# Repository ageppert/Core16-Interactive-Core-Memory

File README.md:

# Core-16-Interactive-Core-Memory-Badge
Weave your own 16 bits of core memory over the top of LEDs to interact with directly using a magnetic wand. This project shares the same codebase as Core64. 

Purchase: https://www.Core64.io

Follow this project at: https://hackaday.io/project/191834-core16-interactive-core-memory-made-smaller

You are in the hardware development repository. Firmware is at https://github.com/ageppert/Core64/releases

# Hardware Version History (latest on top)

v0.2 Logic Board - First production batch

v0.1 Logic Board - Prototype Build

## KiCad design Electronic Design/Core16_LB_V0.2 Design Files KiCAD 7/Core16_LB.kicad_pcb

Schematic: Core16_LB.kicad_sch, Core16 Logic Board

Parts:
C1, C16, C17, C19: 0.1uF; C_0805_2012Metric; LCSC C28233
C7, C8, C9, C13, C14, C15: 220uF; C_1206_3216Metric; LCSC C412252
C10, C12: 1uF; C_0805_2012Metric; LCSC C28323
C11: 0.01uF; C_0805_2012Metric; LCSC C1710
C18: 10uF; C_0805_2012Metric; LCSC C17024
C20, C21, C22, C23: 0.1uF; C_0805_2012Metric; LCSC C396718
CM1: Core_Memory_4x4_Matrix_Front_Facing; core_16_6.75mm_square_front_facing
D1, D3, D9: BAT54CW; SOT-323_SC-70; MPN BAT54CW-7-F; LCSC C83573
D2, D4, D10: BAT54AW; SOT-323_SC-70; MPN BAT54AW-7-F; LCSC C78261
D21, D22, D23, D24, D25, D26, D27, D28, D29, D30, D31, D32, D33, D34, D35, D36: SK6812; 4960_ADA_REV_RGB_LED_short_pads; MPN SK6812-E; Digi-Key_PN 1528-4960-ND
J3: ALT. BATT.; PinSocket_1x02_P2.54mm_Vertical
L1: Core_64_Logo; Core16_w_core_symbol
L3: Core_64_M-+S_Buttons_4mm; Core64-M_-_+_S_Buttons
NT1, NT9, NT11: NetTie_2; NetTie-2_SMD_Pad0.5mm
NT5: GMEM_MON; NetTie-2_THT_Pad0.3mm
NT10: CM_CUR_MON; NetTie-2_SMD_Pad0.5mm
Q1, Q5, Q7, Q9, Q11, Q13, Q17, Q19: MMBT4403LT1G; SOT-23-3; MPN MMBT4403LT1G; Digi-Key_PN MMBT4403LT1GOSCT-ND
Q2, Q6, Q8, Q10, Q12, Q14, Q18, Q20: MMBT4401LT1G; SOT-23-3; MPN MMBT4401LT1G; Digi-Key_PN MMBT4401LT1GOSCT-ND
Q21: NVTR4503NT1G_NMOS_GSD; SOT-23-3; MPN NVTR4503NT1G; LCSC C20917
Q22, Q23: SL3401A; SOT-23-3; MPN SL3401A-TP; LCSC C350311
R1, R2, R5, R6, R7, R8, R9, R10, R11, R12, R13, R14, R17, R18, R19, R20, R28, R46: 470; R_0805_2012Metric; LCSC C17710
R21, R22, R23, R24, R25, R26: 6R8-5%; R_0805_2012Metric; LCSC C17774
R27, R36, R37, R38, R44, R101, R102, R103, R104: 10K; R_0805_2012Metric; LCSC C269724
R30, R31, R41, R42, R43, R54, R55: 1K2; R_0805_2012Metric; LCSC C17379
R32, R33: 68; R_0805_2012Metric; LCSC C17802
R47, R50, R53: 1K5-1%; R_0805_2012Metric; LCSC C4310
R48, R51: 1K8-1%; R_0805_2012Metric; LCSC C17398
R49, R52: 11-1%; R_0805_2012Metric; LCSC C17430
SW1: SK12D07L4B; SK12D07VG4; MPN OS102011MA1QN1; LCSC C480340
U1: PICO W; Pico_SC0915_THRUHOLE_CUTOUTS
U2: M24C02-RMN; SOIC-8_3.9x4.9mm_P1.27mm; MPN M24C02-WMN6TP; LCSC C7562
U7: TLV75533PDBVR; SOT-23-5; MPN ME6211C33M5G-N; LCSC C82942
U8: SN74LV1T125DBVR; SOT-23-5; MPN SN74LV1T125DBVR; LCSC C473338
U9: LM393; SOIC-8_W3.9mm; MPN LM393DT; LCSC C7955
U10: SN74HC02DR; SOIC-14_3.9x8.7mm_P1.27mm; MPN SN74HC02DR; LCSC C350559
U11: SI7210-B-00-IV; SOT-23-5; MPN SI7210-B-00-IV; Digi-Key_PN 336-4068-ND
U12: SI7210-B-02-IV; SOT-23-5; MPN SI7210-B-02-IV; Digi-Key_PN 336-SI7210-B-02-IV-ND
U13: SI7210-B-03-IV; SOT-23-5; MPN SI7210-B-03-IV; Digi-Key_PN 336-SI7210-B-03-IV-ND
U14: SI7210-B-04-IV; SOT-23-5; MPN SI7210-B-04-IV; Digi-Key_PN 336-4056-ND
X8: SAO_conn_SFH11-NBPC-D03-ST-BK; Badgelife-SAOv169-BADGE-2x3; MPN SFH11-NBPC-D03-ST-BK
X9: QWIIC; JST_SH_SM04B-SRSS-TB_1x04-1MP_P1.00mm_Horizontal; MPN SM04B-SRSS-TB; LCSC C160404

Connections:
3V3: C1.1, C12.1, C13.1, C14.1, C15.1, C17.1, C18.1, C19.1, C20.1, C21.1, C22.1, C23.1, NT10.1, R30.1, R31.1, R48.1, R51.1, R54.1, R55.1, R101.1, R102.1, R103.1, R104.1, U2.1 (E0), U2.2 (E1), U2.3 (E2), U2.8 (VCC), U7.5 (OUT), U9.8 (V+), U10.14 (VCC), U11.4 (VDD), U12.4 (VDD), U13.4 (VDD), U14.4 (VDD), X8.1 (3V3), X9.2
5V0: C7.1, C8.1, C9.1, C10.1, C16.1, D21.1 (VDD), D22.1 (VDD), D23.1 (VDD), D24.1 (VDD), D25.1 (VDD), D26.1 (VDD), D27.1 (VDD), D28.1 (VDD), D29.1 (VDD), D30.1 (VDD), D31.1 (VDD), D32.1 (VDD), D33.1 (VDD), D34.1 (VDD), D35.1 (VDD), D36.1 (VDD), NT11.2, Q23.3 (D), U7.1 (IN), U7.3 (EN), U8.5 (VCC)
5VUSB: NT9.2, Q23.1 (G), SW1.1 (A)
+BATT: J3.1, SW1.3 (C)
+VSW: NT11.1, Q22.2 (S), R36.2
-BATT: C1.2, C7.2, C8.2, C9.2, C10.2, C11.2, C12.2, C13.2, C14.2, C15.2, C16.2, C17.2, C18.2, C19.2, C20.2, C21.2, C22.2, C23.2, D21.3 (GND), D22.3 (GND), D23.3 (GND), D24.3 (GND), D25.3 (GND), D26.3 (GND), D27.3 (GND), D28.3 (GND), D29.3 (GND), D30.3 (GND), D31.3 (GND), D32.3 (GND), D33.3 (GND), D34.3 (GND), D35.3 (GND), D36.3 (GND), J3.2, Q21.2 (S), R27.1, R38.2, R44.2, R50.2, R53.2, U1.3 (GND), U1.8 (GND), U1.13 (GND), U1.18 (GND), U1.23 (GND), U1.28 (GND), U1.33 (AGND/GND), U1.38 (GND), U2.4 (VSS), U2.7 (~WC), U7.2 (GND), U8.1 (/OE), U8.3 (GND), U9.4 (V-), U10.7 (GND), U11.2 (GND), U12.2 (GND), U13.2 (GND), U14.2 (GND), X8.2 (GND), X9.1
/ADC0: R41.1, U1.31 (I2C1_SDA/ADC0/GP26)
/ADC0_BUFF: R37.1, R38.1, R41.2
/ADC1: R42.1, U1.32 (I2C1_SCL/ADC1/GP27)
/ADC2: R43.1, U1.34 (ADC2/GP28)
/CA_SENSE_1_OUT: R55.2, U9.7, U10.3
/CA_SENSE_2_OUT: R54.2, U9.1, U10.2
/CM_EN: R27.2, R28.1, U1.26 (I2C0_SDA/GP20)
/CM_Q1N: NT1.2, R2.2, U1.4 (I2C1_SDA/SPI0_SCK/GP2)
/CM_Q1P: R1.2, U1.2 (UART0_RX/I2C0_SCL/GPI0_CSn/GP1)
/CM_Q3N: R6.2, U1.6 (UART1_TX/I2C0_SDA/SPI0_RX/GP4)
/CM_Q3P: R5.2, U1.5 (I2C1_SCL/SPI0_TX/GP3)
/CM_Q4N: R8.2, U1.9 (I2C1_SDA/SPI0_SCK/GP6)
/CM_Q4P: R7.2, U1.7 (UART1_RX/I2C0_SCL/SPI0_CSn/GP5)
/CM_Q5N: R10.2, U1.11 (UART1_TX/I2C0_SDA/SPI1_RX/GP8)
/CM_Q5P: R9.2, U1.10 (I2C1_SCL/SPI0_TX/GP7)
/CM_Q6N: R12.2, U1.16 (UART0_TX/I2C0_SDA/GPI1_RX/GP12)
/CM_Q6P: R11.2, U1.12 (UART1_RX/I2C0_SCL/SPI1_CSn/GP9)
/CM_Q7N: R14.2, U1.19 (I2C1_SDA/SPI1_SCK/GP14)
/CM_Q7P: R13.2, U1.17 (UART0_RX/I2C0_SCL/SPI1_CSn/GP13)
/CM_Q9N: R18.2, U1.21 (UART0_TX/I2C0_SDA/SPI0_RX/GP16)
/CM_Q9P: R17.2, U1.20 (I2C1_SCL/SPI1_TX/GP15)
/CM_Q10N: R20.2, U1.25 (I2C1_SCL/SPI0_TX/GP19)
/CM_Q10P: R19.2, U1.24 (I2C1_SDA/SPI0_SCK/GP18)
/CM_SENSE_1_IN: CM1.17 (S1), R47.1, R52.2, R53.1, U9.5 (+)
/CM_SENSE_2_IN: CM1.18 (S2), R47.2, R49.2, R50.1, U9.3 (+)
/CM_SENSE_PULSE: U1.27 (I2C0_SCL/GP21), U10.10, U10.11
/CM_SENSE_RESET: U1.1 (UART0_TX/I2C0_SDA/SPI0_RX/GP0), U10.8
/GPIO1_SAO1: NT1.1, X8.5 (GPIO1)
/GPIO2_SAO2: U1.22 (UART0_RX/I2C0_SCL/SPI0_CSn/GP17), X8.6 (GPIO2)
/I2C_3V3_SCL: R32.2, U2.6 (SCL), U11.3 (SCL), U12.3 (SCL), U13.3 (SCL), U14.3 (SCL), X8.4 (SCL), X9.4
/I2C_3V3_SDA: R33.1, U2.5 (SDA), U11.1 (SDA), U12.1 (SDA), U13.1 (SDA), U14.1 (SDA), X8.3 (SDA), X9.3
/I2C_CLOCK: R30.2, R32.1, U1.15 (I2C1_SCL/SPI1_TX/GP11)
/I2C_DATA: R31.2, R33.2, U1.14 (I2C1_SDA/SPI1_SCK/GP10)
/LED_ARY_3V3_SIG: U1.29 (GP22), U8.2 (A)
/LED_ARY_5V0_SIG: D21.4 (DIN), R46.1
/XB0: CM1.12 (XB0), D1.1, D2.2
/XB1: CM1.11 (XB1), D1.2, D2.1
/XB2: CM1.10 (XB2), D3.1, D4.2
/XB3: CM1.9 (XB3), D3.2, D4.1
/XT0: CM1.1 (XT0), R21.2
/XT1: CM1.2 (XT1), R22.1
/XT2: CM1.3 (XT2), R23.1
/XT3: CM1.4 (XT3), R24.1
/YL0: CM1.16 (YL0), D9.2, D10.1
/YL0,2: CM1.5 (YR0), CM1.7 (YR2)
/YL1: CM1.15 (YL1), D9.1, D10.2
/YL1,3: CM1.6 (YR1), CM1.8 (YR3)
/YL2: CM1.14 (YL2), R25.1
/YL3: CM1.13 (YL3), R26.1
GMEM: NT5.2, Q2.2 (E), Q6.2 (E), Q8.2 (E), Q10.2 (E), Q12.2 (E), Q14.2 (E), Q18.2 (E), Q20.2 (E), R43.2
unnamed: D21.2 (DOUT), D22.4 (DIN)
unnamed: D22.2 (DOUT), D23.4 (DIN)
unnamed: D23.2 (DOUT), D24.4 (DIN)
unnamed: D24.2 (DOUT), D25.4 (DIN)
unnamed: D25.2 (DOUT), D26.4 (DIN)
unnamed: D26.2 (DOUT), D27.4 (DIN)
unnamed: D27.2 (DOUT), D28.4 (DIN)
unnamed: D28.2 (DOUT), D29.4 (DIN)
unnamed: D29.2 (DOUT), D30.4 (DIN)
unnamed: D30.2 (DOUT), D31.4 (DIN)
unnamed: D31.2 (DOUT), D32.4 (DIN)
unnamed: D32.2 (DOUT), D33.4 (DIN)
unnamed: D33.2 (DOUT), D34.4 (DIN)
unnamed: D34.2 (DOUT), D35.4 (DIN)
unnamed: D35.2 (DOUT), D36.4 (DIN)
unnamed: Q1.1 (B), R1.1
unnamed: D2.3, D4.3, Q1.3 (C)
unnamed: Q2.1 (B), R2.1
unnamed: D1.3, D3.3, Q2.3 (C)
unnamed: Q5.1 (B), R5.1
unnamed: Q5.3 (C), Q6.3 (C), R21.1
unnamed: Q6.1 (B), R6.1
unnamed: Q7.1 (B), R7.1
unnamed: Q7.3 (C), Q8.3 (C), R22.2
unnamed: Q8.1 (B), R8.1
unnamed: Q9.1 (B), R9.1
unnamed: Q10.1 (B), R10.1
unnamed: Q9.3 (C), Q10.3 (C), R23.2
unnamed: Q11.1 (B), R11.1
unnamed: Q11.3 (C), Q12.3 (C), R24.2
unnamed: Q12.1 (B), R12.1
unnamed: Q13.1 (B), R13.1
unnamed: D10.3, Q13.3 (C)
unnamed: Q14.1 (B), R14.1
unnamed: D9.3, Q14.3 (C)
unnamed: Q17.1 (B), R17.1
unnamed: Q17.3 (C), Q18.3 (C), R25.2
unnamed: Q18.1 (B), R18.1
unnamed: Q19.1 (B), R19.1
unnamed: Q19.3 (C), Q20.3 (C), R26.2
unnamed: Q20.1 (B), R20.1
unnamed: NT5.1, Q21.3 (D)
unnamed: Q21.1 (G), R28.2
unnamed: Q22.3 (D), SW1.2 (B)
unnamed: Q22.1 (G), R44.1
unnamed: R36.1, R37.2
unnamed: C11.1, U7.4 (NC)
unnamed: R46.2, U8.4 (Y)
unnamed: R51.2, R52.1, U9.2 (-)
unnamed: R48.2, R49.1, U9.6 (_)
unnamed: U10.1, U10.5, U10.6
unnamed: U10.4, U10.12
unnamed: U10.9, U10.13
unnamed: R101.2, U11.5 (ALERT)
unnamed: R102.2, U12.5 (ALERT)
unnamed: R103.2, U13.5 (ALERT)
unnamed: R104.2, U14.5 (ALERT)
PICO_3V3OUT: U1.35 (ADC_VREF), U1.36 (3V3OUT)
PICO_VBUS: NT9.1, U1.40 (VBUS)
PICO_VSYS: Q23.2 (S), U1.39 (VSYS)
VMEM: NT10.2, Q1.2 (E), Q5.2 (E), Q7.2 (E), Q9.2 (E), Q11.2 (E), Q13.2 (E), Q17.2 (E), Q19.2 (E), R42.2

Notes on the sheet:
Bits 3-0
SILKSCREEN FRONT
INCLUDED:
QxP (PNP) is normally high, low to activate matrix transistor.
AMBIENT PROX. SENSOR OLED AND!XOR IO Exp. MCP23017 AND!XOR EEPROM AT24C32r NFC CLICK PN7120
P-CHNL
C7-9,10-15 D - H - J3 JP - NT9,10,11 Q22-23 R44 SW1 TP - U7 X -
HACKER PLAYGROUND
https://hackaday.io/project/175182-simple-add-ons-sao using Sullins SFH11-NBPC-D03-ST-BK female header https://www.digikey.com/product-detail/en/sullins-connector-solutions/ SFH11-NBPC-D03-ST-BK/S9717-ND/4558818
DIGITAL LOGIC GROUND
SAO #1 SIMPLE ADD-ONS
Bits 15-12
Core16: Removed battery access along with the stacked headers.
I2C ADDRESS TABLE
This diode is built-in to the Pico.
C16 D21-36 H - J - JP - NT - Q - R36-30, 41-43, 46, 101-104 SW - TP - U8,11-14 X8-9
POWER FLOW MORE DETAIL IN CORE64 USER GUIDE
Rds(ON)=0.1
Pico has incoming USB power/programming on board.
COL 0
B_M
DNI
PICO MICROCONTROLLER
C - D1-4, 9-10 H - J - JP - NT5 Q1-20, 21 R1-20, 21-26, 27-28 SW - TP - U - X -
HALL SENSORS
Core16: Removed net-ties and core column 0 / row 0 voltage monitors.
L1-???
SENSE SIGNAL OUTPUT LATCH
NOR -> NOT -> RS LATCH
CORE MATRIX ROW DRIVERS
Pixels 0-3
TWO POWER INPUT SOURCES SELECTED BY SPDT SWITCH. Power Switch ON (BAT), USB cable is NOT connected: P-FET (gate is low) conducts 5V0 (or less if the battery is less than about 5.2V) so that PICO_SYS is powered. PICO_VBUS is not energized because of built-in Zener diode on the Pico. Power Switch OFF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
Default: VMEM (3V3_MON)
CORE MATRIX BOTTOM COLUMN DRIVERS
CORE16: flipped switch inputs so UP is ON when installed on PCB
SOT-23-5 .238VDROP@500mA
Core16: Moved LED driver to lower left sheet.
QxN (NPN) is normally low, high to activate matrix transistor.
BOARD ID AND S/N
OFF (USB)

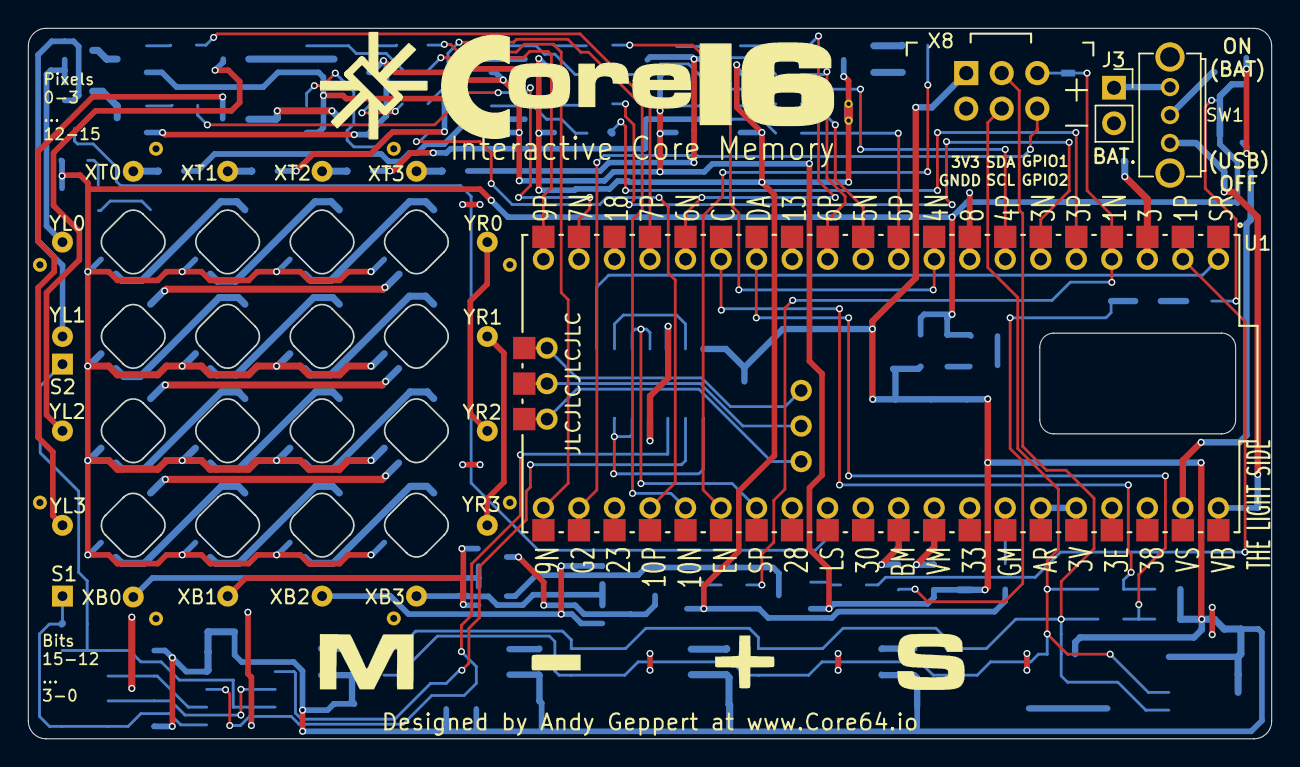
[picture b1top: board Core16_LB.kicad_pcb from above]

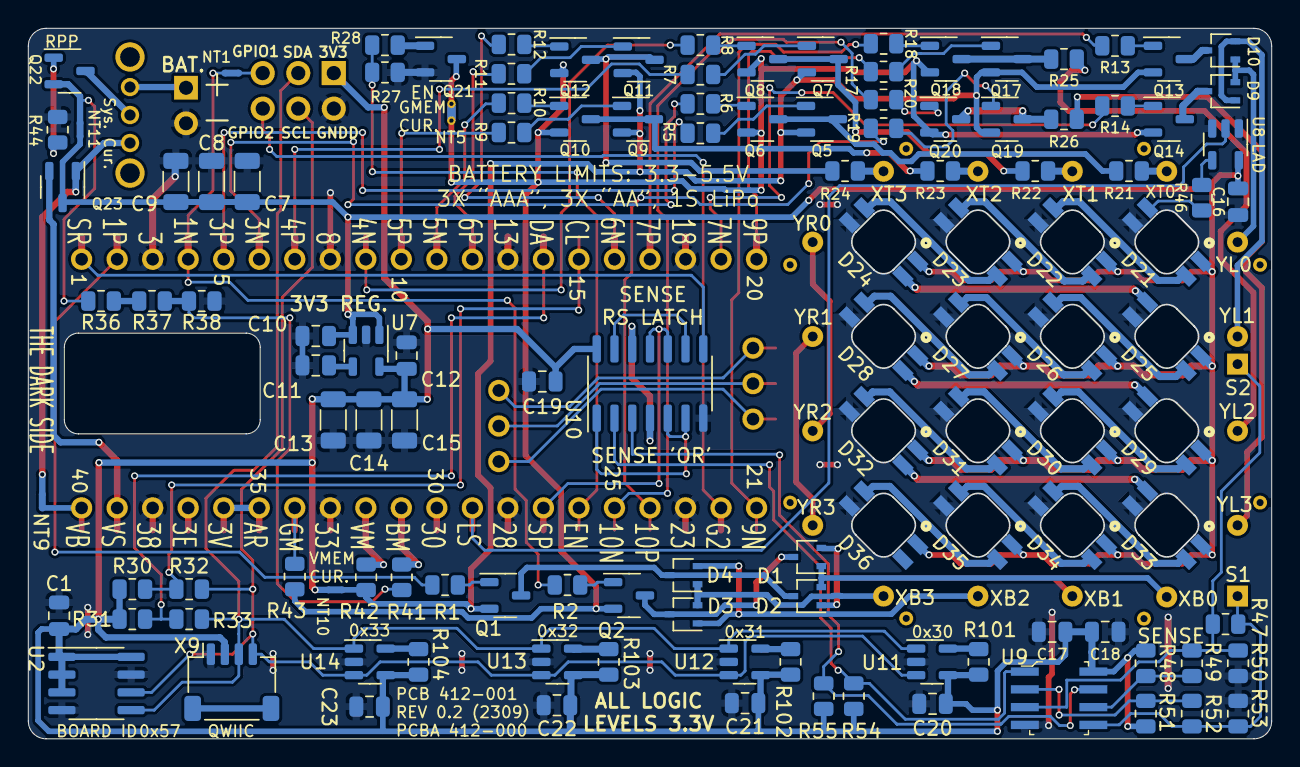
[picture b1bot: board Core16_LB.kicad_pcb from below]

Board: 2 copper layers, 88.8 x 50.7 mm, 130 parts (107 on the bottom side), 117 nets.

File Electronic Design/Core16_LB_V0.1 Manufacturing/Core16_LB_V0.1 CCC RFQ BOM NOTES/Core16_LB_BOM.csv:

"Reference","Value","Footprint","Description","Digi-Key_PN","Insert","LCSC","MPN","MPN(Secondary)","Manufacturer","Manufacturer(Secondary)","Mouser Part Number","Value_Modifier","Qty"
"C1, C16, C17, C19-C23","0.1uF","Capacitor_SMD:C_0805_2012Metric","Capacitor 0805 0.1uF","","YES","-- mixed values --","","","","","","X7R ceramic","8"
"C7-C9, C13-C15","220uF","Capacitor_SMD:C_1206_3216Metric","Capacitor 1206 220uF","","YES","C412252","","","","","","","6"
"C10, C12","1uF","Capacitor_SMD:C_0805_2012Metric","Capacitor 0805 1uF","","YES","C28323","","","","","","","2"
"C11","0.01uF","Capacitor_SMD:C_0805_2012Metric","Capacitor 0805 0.01uF","","YES","C1710","","","","","","","1"
"C18","10uF","Capacitor_SMD:C_0805_2012Metric","Capacitor 0805 10uF","","YES","C17024","","","","","","","1"
"CM1","Core_Memory_4x4_Matrix_Front_Facing","Core_64_KiCad_Library:core_16_6.75mm_square_front_facing","","","NO","","","","","","","","1"
"D1, D3, D9","BAT54CW","Package_TO_SOT_SMD:SOT-323_SC-70","DIODE ARRAY SCHOTTKY 30V ","BAT54CW-FDITR-ND","YES","C83573","BAT54CW-7-F","","Diodes Inc.","","","","3"
"D2, D4, D10","BAT54AW","Package_TO_SOT_SMD:SOT-323_SC-70","DIODE ARRAY SCHOTTKY 30V ","BAT54AW-FDITR-ND","YES","C78261","BAT54AW-7-F","","Diodes Inc.","","","","3"
"D21-D36","SK6812","Core_64_KiCad_Library:4960_ADA_REV_RGB_LED_short_pads","NEOPIXEL REVERSE MOUNT RGB LED","1528-4960-ND","NO","","SK6812-E","","DONGGUAN OPSCO OPTOELECTRONICS","","485-4960","","16"
"J3","ALT. BATT.","Connector_PinSocket_2.54mm:PinSocket_1x02_P2.54mm_Vertical","","","NO","","","","","","","","1"
"L1","Core_64_Logo","Core_64_KiCad_Library:Core16_w_core_symbol","","","NO","","","","","","","","1"
"L3","Core_64_M-+S_Buttons_4mm","Core_64_KiCad_Library:Core64-M_-_+_S_Buttons","","","NO","","","","","","","","1"
"NT1, NT9, NT11","NetTie_2","NetTie:NetTie-2_SMD_Pad0.5mm","","","NO","","","","","","","","3"
"NT5","GMEM_MON","NetTie:NetTie-2_THT_Pad0.3mm","","","NO","","","","","","","","1"
"NT10","CM_CUR_MON","NetTie:NetTie-2_SMD_Pad0.5mm","","","NO","","","","","","","","1"
"Q1, Q5, Q7, Q9, Q11, Q13, Q17, Q19","MMBT4403LT1G","Package_TO_SOT_SMD:SOT-23-3","TRANS PNP 40V 0.6A SOT23","MMBT4403LT1GOSCT-ND","YES","C78864","MMBT4403LT1G","MMBT4403-7-F","ON Semiconductor","Diodes Inc.","","","8"
"Q2, Q6, Q8, Q10, Q12, Q14, Q18, Q20","MMBT4401LT1G","Package_TO_SOT_SMD:SOT-23-3","TRANS NPN 40V 0.6A SOT23","MMBT4401LT1GOSCT-ND","YES","C31776","MMBT4401LT1G","MMBT4401-7-F","ON Semiconductor","Diodes Inc.","","","8"
"Q21","NVTR4503NT1G_NMOS_GSD","Package_TO_SOT_SMD:SOT-23-3","MOSFET N-CHNL GSD LOW RDS(ON)","NVTR4503NT1GOSTR-ND","YES","C20917","NVTR4503NT1G","IRLML2030TRPBF","ON Semiconductor","Infineon Technologies","","","1"
"Q22, Q23","SL3401A","Package_TO_SOT_SMD:SOT-23-3","P-Channel 30V 4.2A 2V @ 250uA 50mΩ @ 4.2A,10V 1.4W SOT-23 MOSFETs RoHS","353-SL3401A-TPTR-ND","YES","C350311","SL3401A-TP","","Micro Commercial Co","","","","2"
"R1, R2, R5-R14, R17-R20, R28, R46","470","Resistor_SMD:R_0805_2012Metric","RES 470 OHM","","YES","C17710","","","","","","10%","18"
"R21-R26","6R8-5%","Resistor_SMD:R_0805_2012Metric","RES  6.8 OHM 1/8W","","YES","C17774","","","","","","5%","6"
"R27, R36-R38, R44","10k","Resistor_SMD:R_0805_2012Metric","RES 10K OHM","","YES","C17414","","","","","","-- mixed values --","5"
"R30, R31, R54, R55","1K2","Resistor_SMD:R_0805_2012Metric","RES 1.2K OHM","","YES","C17379","","","","","","10%","4"
"R32, R33","68","Resistor_SMD:R_0805_2012Metric","RES 68 OHM","","YES","C17802","","","","","","10%","2"
"R41-R43","1k2","Resistor_SMD:R_0805_2012Metric","RES 10K OHM","","YES","C17379","","","","","","20%","3"
"R47, R50, R53","1K5-1%","Resistor_SMD:R_0805_2012Metric","RES 1.5K OHM","","YES","C4310","","","","","","1%","3"
"R48, R51","1K8-1%","Resistor_SMD:R_0805_2012Metric","RES 1.8K OHM","","YES","C17398","","","","","","1%","2"
"R49, R52","11-1%","Resistor_SMD:R_0805_2012Metric","RES 1 OHM","","YES","C17430","","","","","","1%","2"
"R101-R104","10K","Resistor_SMD:R_0805_2012Metric","RES 10K OHM","","YES","C269724","","","","","","10%","4"
"SW1","SK12D07L4B","Switch_XKB_SK12D07VG4_SK12D07L4B:SK12D07VG4","Switch","CKN9559-ND","YES","C480340","OS102011MA1QN1","","C&K","","","","1"
"U1","PICO W","Core_64_KiCad_Library:Pico_SC0915_THRUHOLE_CUTOUTS","Raspberry Pi Pico W","","NO","","","","","","","","1"
"U2","M24C02-RMN","Package_SO:SOIC-8_3.9x4.9mm_P1.27mm","IC EEPROM 2KBIT I2C 400KHZ 8SOIC","497-8552-2-ND","YES","C7562","M24C02-WMN6TP","","STMicroelectronics","","","","1"
"U7","SSP9193-33M5R","Package_TO_SOT_SMD:SOT-23-5","Fixed 3.3V 300mV @ 300mA SOT-23-5 Dropout Regulators(LDO) RoHS","296-TPS7A0533PDBVRTR-ND","YES","C411022","SGM2007-3.3XN5_TR","TPS7A0533PDBVR","SG Micro","TI","","","1"
"U8","SN74LV1T125DBVR","Package_TO_SOT_SMD:SOT-23-5","IC BUF NON-INVERT 5.5V SOT23-5","296-37172-2-ND","YES","C473338","SN74LV1T125DBVR","M74VHC1GT125DT1G","Texas Instruments","OnSemi","","","1"
"U9","LM393","Core_64_KiCad_Library:SOIC-8_W3.9mm","IC COMPARATOR LP DUAL 8-SOIC","497-1593-2-ND","YES","C7955","LM393DT","LM393DR","STMicroelectronics","Rohm","","","1"
"U10","SN74HC02DR","Package_SO:SOIC-14_3.9x8.7mm_P1.27mm","IC GATE NOR 4CH 2-INP 14SOIC","296-1188-2-ND","YES","C350559","SN74HC02DR","","Texas Instruments","","","","1"
"U11","SI7210-B-00-IV","Package_TO_SOT_SMD:SOT-23-5","Si7210 Series I2C Hall Effect Magnetic Position and Temperature Sensor","336-4068-ND","YES","","SI7210-B-00-IV","","Silicon Labs","","","","1"
"U12","SI7210-B-02-IV","Package_TO_SOT_SMD:SOT-23-5","Si7210 Series I2C Hall Effect Magnetic Position and Temperature Sensor","336-SI7210-B-02-IV-ND","YES","","SI7210-B-02-IV","","Silicon Labs","","","","1"
"U13","SI7210-B-03-IV","Package_TO_SOT_SMD:SOT-23-5","Si7210 Series I2C Hall Effect Magnetic Position and Temperature Sensor","336-SI7210-B-03-IV-ND","YES","","SI7210-B-03-IV","","Silicon Labs","","","","1"
"U14","SI7210-B-04-IV","Package_TO_SOT_SMD:SOT-23-5","Si7210 Series I2C Hall Effect Magnetic Position and Temperature Sensor","336-4056-ND","YES","","SI7210-B-04-IV","","Silicon Labs","","","","1"
"X8","SAO_conn_SFH11-NBPC-D03-ST-BK","Core_64_KiCad_Library:Badgelife-SAOv169-BADGE-2x3","CONN HDR 6POS KEYED SOCKET 0.1 T.H.","","NO","","SFH11-NBPC-D03-ST-BK","","Sullins","","","","1"
"X9","QWIIC","Connector_JST:JST_SH_SM04B-SRSS-TB_1x04-1MP_P1.00mm_Horizontal","JST_SH_SM04B-SRSS-TB_1x04","455-SM04B-SRSS-TBTR-ND","YES","C160404","SM04B-SRSS-TB","","JST","","","","1"

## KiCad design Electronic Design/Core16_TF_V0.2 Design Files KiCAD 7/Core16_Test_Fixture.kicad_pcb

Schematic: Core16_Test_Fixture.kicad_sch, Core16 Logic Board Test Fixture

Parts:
C1: 0.1uF; C_0805_2012Metric; LCSC C28233
CM1, CM2: Core_Memory_4x4_Matrix_Front_Facing; core_16_6.75mm_square_front_facing
J1, J2: ALT. BATT.; PinSocket_1x02_P2.54mm_Vertical
J3: Conn_01x18_Socket; PinHeader_1x18_P2.54mm_Vertical
J4, J5: Conn_01x20_Socket; PinHeader_1x20_P2.54mm_Vertical
J6: Conn_01x05_Socket; PinHeader_1x05_P2.54mm_Vertical
J7: Conn_01x06_Socket; PinHeader_1x06_P2.54mm_Vertical
J8: Conn_01x04_Socket; PinHeader_1x04_P2.54mm_Vertical
SW1, SW2: SK12D07L4B; SK12D07VG4; MPN OS102011MA1QN1; LCSC C480340
U1, U2: PICO W; Pico_SC0915_THRUHOLE_CUTOUTS
U3: M24C02-RMN; SOIC-8_3.9x4.9mm_P1.27mm; MPN M24C02-WMN6TP; LCSC C7562
X1, X2: SAO_conn_SFH11-NBPC-D03-ST-BK; Badgelife-SAOv169-BADGE-2x3; MPN SFH11-NBPC-D03-ST-BK
X3: QWIIC; JST_SH_SM04B-SRSS-TB_1x04-1MP_P1.00mm_Horizontal; MPN SM04B-SRSS-TB; LCSC C160404

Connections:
/3V3: C1.1, J7.2, J8.2, U3.2 (E1), U3.3 (E2), U3.8 (VCC), X1.1 (3V3), X2.1 (3V3), X3.2
/3V3_EN: J5.17, U1.37 (3V3_EN), U2.37 (3V3_EN)
/+BATT: J1.1, J2.1, J6.2
/-BATT: J1.2, J2.2, J6.1
/ADC0: J5.11, U1.31 (I2C1_SDA/ADC0/GP26), U2.31 (I2C1_SDA/ADC0/GP26)
/ADC1: J5.12, U1.32 (I2C1_SCL/ADC1/GP27), U2.32 (I2C1_SCL/ADC1/GP27)
/ADC2: J5.14, U1.34 (ADC2/GP28), U2.34 (ADC2/GP28)
/ADC_REF: J5.15, J5.16, U1.35 (ADC_VREF), U1.36 (3V3OUT), U2.35 (ADC_VREF), U2.36 (3V3OUT)
/CM_EN: J5.6, U1.26 (I2C0_SDA/GP20), U2.26 (I2C0_SDA/GP20)
/CM_Q1N: J4.4, U1.4 (I2C1_SDA/SPI0_SCK/GP2), U2.4 (I2C1_SDA/SPI0_SCK/GP2)
/CM_Q1P: J4.2, U1.2 (UART0_RX/I2C0_SCL/GPI0_CSn/GP1), U2.2 (UART0_RX/I2C0_SCL/GPI0_CSn/GP1)
/CM_Q3N: J4.6, U1.6 (UART1_TX/I2C0_SDA/SPI0_RX/GP4), U2.6 (UART1_TX/I2C0_SDA/SPI0_RX/GP4)
/CM_Q3P: J4.5, U1.5 (I2C1_SCL/SPI0_TX/GP3), U2.5 (I2C1_SCL/SPI0_TX/GP3)
/CM_Q4N: J4.9, U1.9 (I2C1_SDA/SPI0_SCK/GP6), U2.9 (I2C1_SDA/SPI0_SCK/GP6)
/CM_Q4P: J4.7, U1.7 (UART1_RX/I2C0_SCL/SPI0_CSn/GP5), U2.7 (UART1_RX/I2C0_SCL/SPI0_CSn/GP5)
/CM_Q5N: J4.11, U1.11 (UART1_TX/I2C0_SDA/SPI1_RX/GP8), U2.11 (UART1_TX/I2C0_SDA/SPI1_RX/GP8)
/CM_Q5P: J4.10, U1.10 (I2C1_SCL/SPI0_TX/GP7), U2.10 (I2C1_SCL/SPI0_TX/GP7)
/CM_Q6N: J4.16, U1.16 (UART0_TX/I2C0_SDA/GPI1_RX/GP12), U2.16 (UART0_TX/I2C0_SDA/GPI1_RX/GP12)
/CM_Q6P: J4.12, U1.12 (UART1_RX/I2C0_SCL/SPI1_CSn/GP9), U2.12 (UART1_RX/I2C0_SCL/SPI1_CSn/GP9)
/CM_Q7N: J4.19, U1.19 (I2C1_SDA/SPI1_SCK/GP14), U2.19 (I2C1_SDA/SPI1_SCK/GP14)
/CM_Q7P: J4.17, U1.17 (UART0_RX/I2C0_SCL/SPI1_CSn/GP13), U2.17 (UART0_RX/I2C0_SCL/SPI1_CSn/GP13)
/CM_Q9N: J5.1, U1.21 (UART0_TX/I2C0_SDA/SPI0_RX/GP16), U2.21 (UART0_TX/I2C0_SDA/SPI0_RX/GP16)
/CM_Q9P: J4.20, U1.20 (I2C1_SCL/SPI1_TX/GP15), U2.20 (I2C1_SCL/SPI1_TX/GP15)
/CM_Q10N: J5.5, U1.25 (I2C1_SCL/SPI0_TX/GP19), U2.25 (I2C1_SCL/SPI0_TX/GP19)
/CM_Q10P: J5.4, U1.24 (I2C1_SDA/SPI0_SCK/GP18), U2.24 (I2C1_SDA/SPI0_SCK/GP18)
/CM_SENSE_1_IN: CM1.17 (S1), CM2.17 (S1), J3.17
/CM_SENSE_2_IN: CM1.18 (S2), CM2.18 (S2), J3.18
/CM_SENSE_PULSE: J5.7, U1.27 (I2C0_SCL/GP21), U2.27 (I2C0_SCL/GP21)
/CM_SENSE_RESET: J4.1, U1.1 (UART0_TX/I2C0_SDA/SPI0_RX/GP0), U2.1 (UART0_TX/I2C0_SDA/SPI0_RX/GP0)
/GPIO1_SAO1: J7.5, X1.5 (GPIO1), X2.5 (GPIO1)
/GPIO2_SAO2: J5.2, J7.6, U1.22 (UART0_RX/I2C0_SCL/SPI0_CSn/GP17), U2.22 (UART0_RX/I2C0_SCL/SPI0_CSn/GP17), X1.6 (GPIO2), X2.6 (GPIO2)
/I2C_3V3_SCL: J7.3, J8.3, U3.6 (SCL), X1.4 (SCL), X2.4 (SCL), X3.4
/I2C_3V3_SDA: J7.4, J8.4, U3.5 (SDA), X1.3 (SDA), X2.3 (SDA), X3.3
/I2C_CLOCK: J4.15, U1.15 (I2C1_SCL/SPI1_TX/GP11), U2.15 (I2C1_SCL/SPI1_TX/GP11)
/I2C_DATA: J4.14, U1.14 (I2C1_SDA/SPI1_SCK/GP10), U2.14 (I2C1_SDA/SPI1_SCK/GP10)
/LED_ARY_3V3_SIG: J5.9, U1.29 (GP22), U2.29 (GP22)
/OFF (USB): J6.5, SW1.1 (A), SW2.1 (A)
/ON_BAT: J6.3, SW1.3 (C), SW2.3 (C)
/PICO_VBUS: J5.20, U1.40 (VBUS), U2.40 (VBUS)
/PICO_VSYS: J5.19, U1.39 (VSYS), U2.39 (VSYS)
/RUN: J5.10, U1.30 (RUN), U2.30 (RUN)
/VSW: J6.4, SW1.2 (B), SW2.2 (B)
/XB0: CM1.12 (XB0), CM2.12 (XB0), J3.5
/XB1: CM1.11 (XB1), CM2.11 (XB1), J3.6
/XB2: CM1.10 (XB2), CM2.10 (XB2), J3.7
/XB3: CM1.9 (XB3), CM2.9 (XB3), J3.8
/XT0: CM1.1 (XT0), CM2.1 (XT0), J3.1
/XT1: CM1.2 (XT1), CM2.2 (XT1), J3.2
/XT2: CM1.3 (XT2), CM2.3 (XT2), J3.3
/XT3: CM1.4 (XT3), CM2.4 (XT3), J3.4
/YL0: CM1.16 (YL0), CM2.16 (YL0), J3.9
/YL1: CM1.15 (YL1), CM2.15 (YL1), J3.10
/YL2: CM1.14 (YL2), CM2.14 (YL2), J3.11
/YL3: CM1.13 (YL3), CM2.13 (YL3), J3.12
/YR0: CM1.5 (YR0), CM2.5 (YR0), J3.13
/YR1: CM1.6 (YR1), CM2.6 (YR1), J3.14
/YR2: CM1.7 (YR2), CM2.7 (YR2), J3.15
/YR3: CM1.8 (YR3), CM2.8 (YR3), J3.16
GNDD: C1.2, J4.3, J4.8, J4.13, J4.18, J5.3, J5.8, J5.13, J5.18, J7.1, J8.1, U1.3 (GND), U1.8 (GND), U1.13 (GND), U1.18 (GND), U1.23 (GND), U1.28 (GND), U1.33 (AGND/GND), U1.38 (GND), U2.3 (GND), U2.8 (GND), U2.13 (GND), U2.18 (GND), U2.23 (GND), U2.28 (GND), U2.33 (AGND/GND), U2.38 (GND), U3.1 (E0), U3.4 (VSS), U3.7 (~WC), X1.2 (GND), X2.2 (GND), X3.1

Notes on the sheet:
INCLUDED:
AMBIENT PROX. SENSOR OLED AND!XOR IO Exp. MCP23017 AND!XOR EEPROM AT24C32r NFC CLICK PN7120
TEST CIRCUIT
SAO
I2C ADDRESS TABLE
Pico has incoming USB power/programming on board.
TEST EEPROM
EEPROM I2C ADDRESS: 0b1010110, 0x56 (86)
CORE TEST
Generic 0.96” (128x64) or 1.5” (128x128) I2C 4-pins, often ADDRESS: 0x3C (60 decimal) Alternate is 0x3D, not 0x7A or 0x78 (wrong 8-bit)!
DUT
CORE MATRIX
PICO
0x29 (47) 0x30 (48) 0x31 (49) 0x32 (50) 0x33 (51) 0x57 (87) 0x56 (86)
OLED
POWER
PICO 21-40
POWER TEST
SYSTEM GROUND
Connect via SAO.
I2C ADDRESS TABLE
AMBIENT LIGHT SENSOR HALL SENSOR 1 HALL SENSOR 2 HALL SENSOR 3 HALL SENSOR 4 EEPROM (BOARD ID) EEPROM (TEST FIXTURE)
PICO 1-20
0x38 (56) 0x3C (60) 0x20 (32) 0x50 (80) 0x50-53
QWIIC I2C
I2C GPIO
OPTIONAL:
All 7-bit addresses should be greater than 0x07 and less than 0x78 (120).
OLED MONOCHROME I2C
DIGITAL LOGIC GROUND PLANE

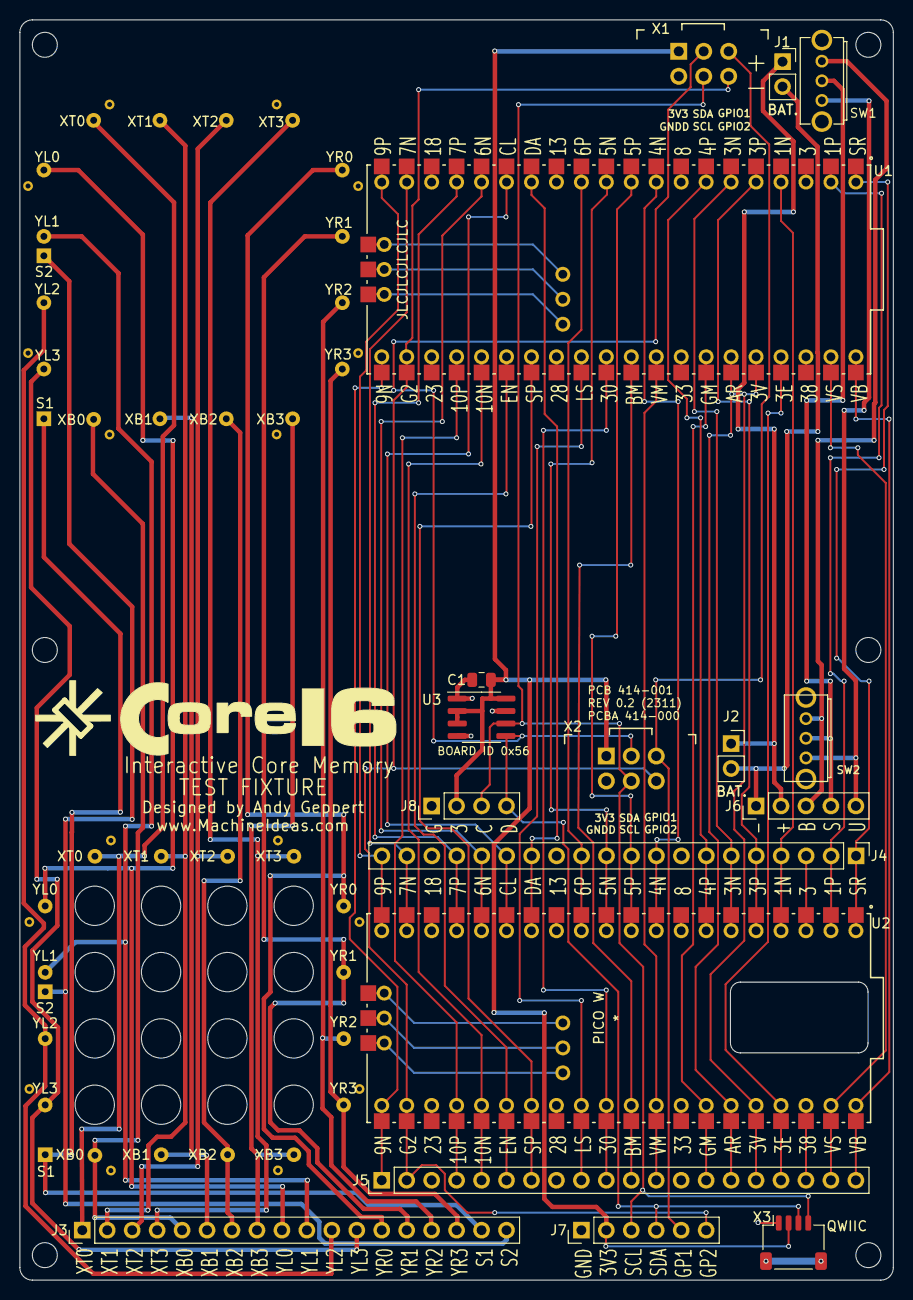
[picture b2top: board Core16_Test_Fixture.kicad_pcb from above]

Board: 2 copper layers, 88.9 x 128.3 mm, 20 parts (0 on the bottom side), 59 nets.

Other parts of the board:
L1: Core_64_Logo; Core16_w_core_symbol

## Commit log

2024-08-11 Organize documentation, add board render images
2024-08-11 Add Troubleshooting Guide draft
2024-08-23 Add Render R47, remove backup files

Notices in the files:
parts and their libraries:
Copyright 2016 Accelerated Designs. All rights reserved.
